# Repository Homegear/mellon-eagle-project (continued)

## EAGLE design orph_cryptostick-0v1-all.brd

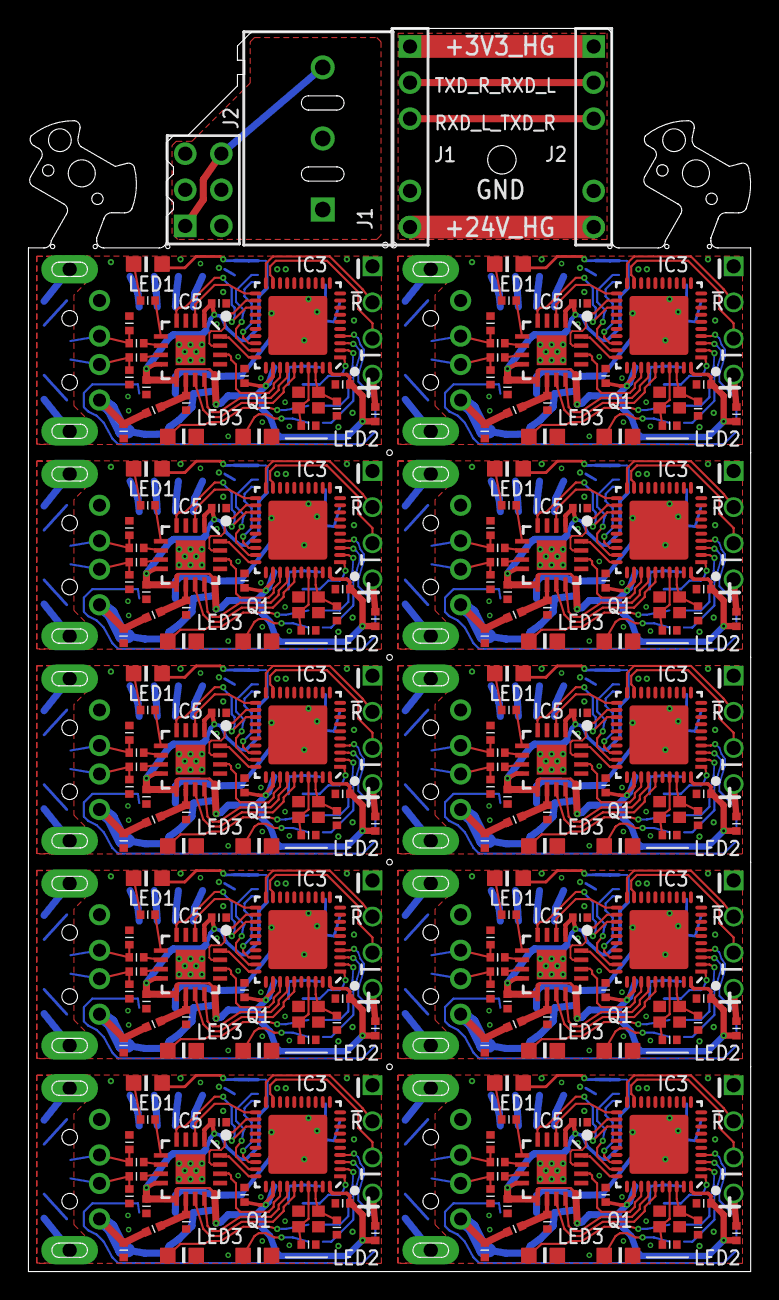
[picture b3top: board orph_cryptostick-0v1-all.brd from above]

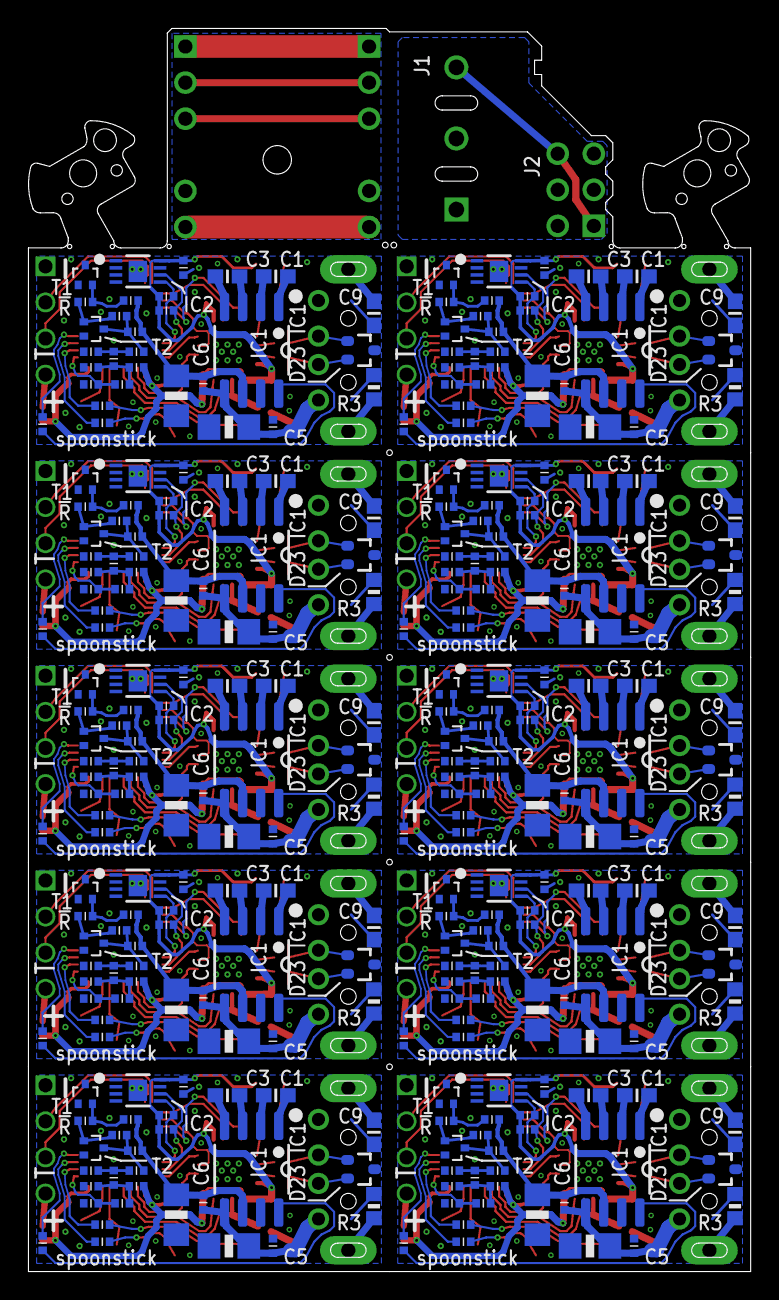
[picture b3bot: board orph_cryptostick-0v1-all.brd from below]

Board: 2 copper layers, 50.8 x 87.4 mm, 534 parts (300 on the bottom side), 428 nets.

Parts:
C1, C3, C23, C24, C47, C48, C68, C69, C89, C95, C115, C116, C136, C137, C157, C158, C178, C179, C199, C200: 0u22; C0603
C2, C4, C7, C10, C12, C16, C17, C18, C19, C20, C21, C25, C28, C30, C31, C33, C34, C40, C41, C42, C43, C44, C45, C49, C52, C54, C55, C61, C62, C63, C64, C65, C66, C70, C73, C75, C76, C82, C83, C84, C85, C86, C87, C92, C93, C94, C96, C99, C101, C102, C108, C109, C110, C111, C112, C113, C117, C120, C122, C123, C129, C130, C131, C132, C133, C134, C138, C141, C143, C144, C150, C151, C152, C153, C154, C155, C159, C162, C164, C165, C171, C172, C173, C174, C175, C176, C180, C183, C185, C186, C192, C193, C194, C195, C196, C197, C201, C204, C206, C207: 0u1; R0402-MCU
C5, C6, C26, C27, C50, C51, C71, C72, C97, C98, C118, C119, C139, C140, C160, C161, C181, C182, C202, C203: 10u/1206; C1206
C8, C11, C29, C35, C53, C56, C74, C77, C100, C103, C121, C124, C142, C145, C163, C166, C184, C187, C205, C208: 22p; R0402-MCU
C9, C36, C57, C78, C104, C125, C146, C167, C188, C209: 10n_nm; C0603
C13, C37, C58, C79, C105, C126, C147, C168, C189, C210: 10n; R0402-MCU
C14, C15, C38, C39, C59, C60, C80, C81, C90, C91, C106, C107, C127, C128, C148, C149, C169, C170, C190, C191: 47p; R0402-MCU
C22, C32, C46, C67, C88, C114, C135, C156, C177, C198: 100p; R0402-MCU
D1, D2, D3, D4, D5, D6, D7, D8, D9, D23: TVS-ESD7002; SC70-3
IC1, IC8, IC12, IC16, IC20, IC24, IC28, IC32, IC36, IC40: ST662-2; 8SOIC-2
IC2, IC6, IC10, IC14, IC18, IC22, IC26, IC30, IC34, IC38: ATECC508A-UDFN; 8UDFN
IC3, IC7, IC11, IC15, IC19, IC23, IC27, IC31, IC35, IC39: MSP430FR5959-40VQFN; 40VQFN-MSP430FR5959
IC4, IC5, IC9, IC13, IC17, IC21, IC25, IC29, IC33, IC37: FT230XQ; 16QFN-FT230X
J1, J7, J9, J11, J13, J15, J17, J19, J21, J23: USB-A-ST
J2: KLEMME-3POS-FEDER-5MM; KLEMME-FEDER-5MM-3POS
J3, J8, J10, J12, J14, J16, J18, J20, J22, J24: FE04-1
J4: FE03-2; FE03-2-R/A
J5, J6: MA06-1-KEY
L1, L2, L3, L4, L5, L6, L7, L8, L9, L10: R0402-MCU
LED1, LED2, LED4, LED5, LED7, LED8, LED10, LED11, LED13, LED14, LED16, LED17, LED19, LED20, LED22, LED23, LED25, LED26, LED28, LED29: green; 0603-SIDELED-RPI
LED3, LED6, LED9, LED12, LED15, LED18, LED21, LED24, LED27, LED30: orange; 0603-SIDELED-RPI
Q1, Q2, Q3, Q4, Q5, Q6, Q7, Q8, Q9, Q10: XTAL-30MHZ-2.0X1.6
R1, R4, R11, R12, R29, R30, R55, R56, R73, R77, R94, R95, R112, R113, R130, R131, R148, R149, R166, R167: 3k9; R0402-MCU
R2, R21, R47, R65, R86, R104, R122, R140, R158, R176: 4k7; R0402-MCU
R3, R22, R48, R66, R87, R105, R123, R141, R159, R177: 1M_nm; R0603
R5, R23, R49, R67, R88, R106, R124, R142, R160, R178: 68; R0402-MCU
R6, R7, R10, R24, R25, R28, R50, R51, R54, R68, R69, R72, R76, R89, R90, R93, R107, R108, R111, R125, R126, R129, R143, R144, R147, R161, R162, R165, R179, R180: 1k; R0402-MCU
R8, R9, R26, R27, R52, R53, R70, R71, R74, R75, R91, R92, R109, R110, R127, R128, R145, R146, R163, R164: 27; R0402-MCU
R13, R31, R33, R57, R78, R96, R114, R132, R150, R168: 100k; R0402-MCU
R14, R32, R34, R58, R79, R97, R115, R133, R151, R169: 1M; R0402-MCU
R15, R19, R35, R39, R41, R45, R59, R63, R80, R84, R98, R102, R116, R120, R134, R138, R152, R156, R170, R174: 10k; R0402-MCU
R16, R17, R18, R20, R36, R37, R38, R40, R42, R43, R44, R46, R60, R61, R62, R64, R81, R82, R83, R85, R99, R100, R101, R103, R117, R118, R119, R121, R135, R136, R137, R139, R153, R154, R155, R157, R171, R172, R173, R175: 33k; R0402-MCU
T1, T2, T3, T4, T5, T6, T7, T8, T9, T10, T11, T12, T13, T14, T15, T16, T17, T18, T19, T20: NPN-MMBT3904-SOT523; SOT523

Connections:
0V: J2.2, J4.3, J4.4
+3V3_FTDI: C2.1, C10.1, C12.1, C93.1, C94.1, IC2.8, IC3.32, IC3.40, IC5.1, IC5.8, IC5.9, LED1.A, R1.1, R4.1, R5.1, R36.1
+3V3_FTDI1: C17.1, C18.1, C19.1, C33.1, C34.1, IC4.1, IC4.8, IC4.9, IC6.8, IC7.32, IC7.40, LED4.A, R11.1, R12.1, R16.1, R23.1
+3V3_FTDI2: C41.1, C42.1, C43.1, C54.1, C55.1, IC9.1, IC9.8, IC9.9, IC10.8, IC11.32, IC11.40, LED7.A, R29.1, R30.1, R42.1, R49.1
+3V3_FTDI3: C62.1, C63.1, C64.1, C75.1, C76.1, IC13.1, IC13.8, IC13.9, IC14.8, IC15.32, IC15.40, LED10.A, R55.1, R56.1, R60.1, R67.1
+3V3_FTDI4: C83.1, C84.1, C85.1, C101.1, C102.1, IC17.1, IC17.8, IC17.9, IC18.8, IC19.32, IC19.40, LED13.A, R73.1, R77.1, R81.1, R88.1
+3V3_FTDI5: C109.1, C110.1, C111.1, C122.1, C123.1, IC21.1, IC21.8, IC21.9, IC22.8, IC23.32, IC23.40, LED16.A, R94.1, R95.1, R99.1, R106.1
+3V3_FTDI6: C130.1, C131.1, C132.1, C143.1, C144.1, IC25.1, IC25.8, IC25.9, IC26.8, IC27.32, IC27.40, LED19.A, R112.1, R113.1, R117.1, R124.1
+3V3_FTDI7: C151.1, C152.1, C153.1, C164.1, C165.1, IC29.1, IC29.8, IC29.9, IC30.8, IC31.32, IC31.40, LED22.A, R130.1, R131.1, R135.1, R142.1
+3V3_FTDI8: C172.1, C173.1, C174.1, C185.1, C186.1, IC33.1, IC33.8, IC33.9, IC34.8, IC35.32, IC35.40, LED25.A, R148.1, R149.1, R153.1, R160.1
+3V3_FTDI9: C193.1, C194.1, C195.1, C206.1, C207.1, IC37.1, IC37.8, IC37.9, IC38.8, IC39.32, IC39.40, LED28.A, R166.1, R167.1, R171.1, R178.1
+3V3_HG: J5.1, J6.1
+5V_FTDI: C92.1, IC5.10, L1.2
+5V_FTDI1: C16.1, IC4.10, L2.2
+5V_FTDI2: C40.1, IC9.10, L3.2
+5V_FTDI3: C61.1, IC13.10, L4.2
+5V_FTDI4: C82.1, IC17.10, L5.2
+5V_FTDI5: C108.1, IC21.10, L6.2
+5V_FTDI6: C129.1, IC25.10, L7.2
+5V_FTDI7: C150.1, IC29.10, L8.2
+5V_FTDI8: C171.1, IC33.10, L9.2
+5V_FTDI9: C192.1, IC37.10, L10.2
+12V: C4.1, C6.1, IC1.6, R33.2, R35.1
+12V1: C25.1, C27.1, IC8.6, R13.2, R15.1
+12V2: C49.1, C51.1, IC12.6, R31.2, R41.1
+12V3: C70.1, C72.1, IC16.6, R57.2, R59.1
+12V4: C96.1, C98.1, IC20.6, R78.2, R80.1
+12V5: C117.1, C119.1, IC24.6, R96.2, R98.1
+12V6: C138.1, C140.1, IC28.6, R114.2, R116.1
+12V7: C159.1, C161.1, IC32.6, R132.2, R134.1
+12V8: C180.1, C182.1, IC36.6, R150.2, R152.1
+12V9: C201.1, C203.1, IC40.6, R168.2, R170.1
+24V: J2.1, J4.2, J4.5
+24V_HG: J5.6, J6.6
+VBUS: C4.2, C5.1, C7.1, C13.1, IC1.5, J1.1, L1.1
+VBUS1: C25.2, C26.1, C28.1, C37.1, IC8.5, J7.1, L2.1
+VBUS2: C49.2, C50.1, C52.1, C58.1, IC12.5, J9.1, L3.1
+VBUS3: C70.2, C71.1, C73.1, C79.1, IC16.5, J11.1, L4.1
+VBUS4: C96.2, C97.1, C99.1, C105.1, IC20.5, J13.1, L5.1
+VBUS5: C117.2, C118.1, C120.1, C126.1, IC24.5, J15.1, L6.1
+VBUS6: C138.2, C139.1, C141.1, C147.1, IC28.5, J17.1, L7.1
+VBUS7: C159.2, C160.1, C162.1, C168.1, IC32.5, J19.1, L8.1
+VBUS8: C180.2, C181.1, C183.1, C189.1, IC36.5, J21.1, L9.1
+VBUS9: C201.2, C202.1, C204.1, C210.1, IC40.5, J23.1, L10.1
CHARGEPUMP_SHDN: IC3.4, R2.2
CHARGEPUMP_SHDN1: IC7.4, R21.2
CHARGEPUMP_SHDN2: IC11.4, R47.2
CHARGEPUMP_SHDN3: IC15.4, R65.2
CHARGEPUMP_SHDN4: IC19.4, R86.2
CHARGEPUMP_SHDN5: IC23.4, R104.2
CHARGEPUMP_SHDN6: IC27.4, R122.2
CHARGEPUMP_SHDN7: IC31.4, R140.2
CHARGEPUMP_SHDN8: IC35.4, R158.2
CHARGEPUMP_SHDN9: IC39.4, R176.2
FTDI_CBUS0: IC3.34, IC5.12
FTDI_CBUS1: IC3.35, IC5.11
FTDI_CBUS2: IC4.11, IC7.35
FTDI_CBUS3: IC4.12, IC7.34
FTDI_CBUS4: IC9.11, IC11.35
FTDI_CBUS5: IC9.12, IC11.34
FTDI_CBUS6: IC13.11, IC15.35
FTDI_CBUS7: IC13.12, IC15.34
FTDI_CBUS8: IC17.11, IC19.35
FTDI_CBUS9: IC17.12, IC19.34
FTDI_CBUS10: IC21.11, IC23.35
FTDI_CBUS11: IC21.12, IC23.34
FTDI_CBUS12: IC25.11, IC27.35
FTDI_CBUS13: IC25.12, IC27.34
FTDI_CBUS14: IC29.11, IC31.35
FTDI_CBUS15: IC29.12, IC31.34
FTDI_CBUS16: IC33.11, IC35.35
FTDI_CBUS17: IC33.12, IC35.34
FTDI_CBUS18: IC37.11, IC39.35
FTDI_CBUS19: IC37.12, IC39.34
FTDI_CTS#: IC3.23, IC5.4
FTDI_CTS#1: IC4.4, IC7.23
FTDI_CTS#2: IC9.4, IC11.23
FTDI_CTS#3: IC13.4, IC15.23
FTDI_CTS#4: IC17.4, IC19.23
FTDI_CTS#5: IC21.4, IC23.23
FTDI_CTS#6: IC25.4, IC27.23
FTDI_CTS#7: IC29.4, IC31.23
FTDI_CTS#8: IC33.4, IC35.23
FTDI_CTS#9: IC37.4, IC39.23
FTDI_RTS#: IC3.30, IC5.16
FTDI_RTS#1: IC4.16, IC7.30
FTDI_RTS#2: IC9.16, IC11.30
FTDI_RTS#3: IC13.16, IC15.30
FTDI_RTS#4: IC17.16, IC19.30
FTDI_RTS#5: IC21.16, IC23.30
FTDI_RTS#6: IC25.16, IC27.30
FTDI_RTS#7: IC29.16, IC31.30
FTDI_RTS#8: IC33.16, IC35.30
FTDI_RTS#9: IC37.16, IC39.30
FTDI_RXD: IC3.21, IC5.2
FTDI_RXD1: IC4.2, IC7.21
FTDI_RXD2: IC9.2, IC11.21
FTDI_RXD3: IC13.2, IC15.21
FTDI_RXD4: IC17.2, IC19.21
FTDI_RXD5: IC21.2, IC23.21
FTDI_RXD6: IC25.2, IC27.21
FTDI_RXD7: IC29.2, IC31.21
FTDI_RXD8: IC33.2, IC35.21
FTDI_RXD9: IC37.2, IC39.21
FTDI_TXD: IC3.22, IC5.15
FTDI_TXD1: IC4.15, IC7.22
FTDI_TXD2: IC9.15, IC11.22
FTDI_TXD3: IC13.15, IC15.22
FTDI_TXD4: IC17.15, IC19.22
FTDI_TXD5: IC21.15, IC23.22
FTDI_TXD6: IC25.15, IC27.22
FTDI_TXD7: IC29.15, IC31.22
FTDI_TXD8: IC33.15, IC35.22
FTDI_TXD9: IC37.15, IC39.22
FTDI_TXLED#: IC5.5, R76.1
FTDI_TXLED#1: IC4.5, R10.1
FTDI_TXLED#2: IC9.5, R28.1
FTDI_TXLED#3: IC13.5, R54.1
FTDI_TXLED#4: IC17.5, R72.1
FTDI_TXLED#5: IC21.5, R93.1
FTDI_TXLED#6: IC25.5, R111.1
FTDI_TXLED#7: IC29.5, R129.1
FTDI_TXLED#8: IC33.5, R147.1
FTDI_TXLED#9: IC37.5, R165.1
GND: C2.2, C5.2, C6.2, C7.2, C8.1, C9.1, C10.2, C11.1, C12.2, C13.2, C32.2, C90.2, C91.2, C92.2, C93.2, C94.2, D23.3, IC1.7, IC2.1, IC2.2, IC2.3, IC2.4, IC2.7, IC2.EP, IC3.31, IC3.36, IC3.39, IC3.EP, IC5.3, IC5.13, IC5.EP, J1.4, J3.1, LED2.C, LED3.C, Q1.2, Q1.4, R3.1, R37.2, R39.2, T1.1, T2.2
GND1: J5.5, J6.5
GND2: C14.2, C15.2, C16.2, C17.2, C18.2, C19.2, C22.2, C26.2, C27.2, C28.2, C29.1, C33.2, C34.2, C35.1, C36.1, C37.2, D1.3, IC4.3, IC4.13, IC4.EP, IC6.1, IC6.2, IC6.3, IC6.4, IC6.7, IC6.EP, IC7.31, IC7.36, IC7.39, IC7.EP, IC8.7, J7.4, J8.1, LED5.C, LED6.C, Q2.2, Q2.4, R17.2, R19.2, R22.1, T3.1, T4.2
GND3: C38.2, C39.2, C40.2, C41.2, C42.2, C43.2, C46.2, C50.2, C51.2, C52.2, C53.1, C54.2, C55.2, C56.1, C57.1, C58.2, D2.3, IC9.3, IC9.13, IC9.EP, IC10.1, IC10.2, IC10.3, IC10.4, IC10.7, IC10.EP, IC11.31, IC11.36, IC11.39, IC11.EP, IC12.7, J9.4, J10.1, LED8.C, LED9.C, Q3.2, Q3.4, R43.2, R45.2, R48.1, T5.1, T6.2
GND4: C59.2, C60.2, C61.2, C62.2, C63.2, C64.2, C67.2, C71.2, C72.2, C73.2, C74.1, C75.2, C76.2, C77.1, C78.1, C79.2, D3.3, IC13.3, IC13.13, IC13.EP, IC14.1, IC14.2, IC14.3, IC14.4, IC14.7, IC14.EP, IC15.31, IC15.36, IC15.39, IC15.EP, IC16.7, J11.4, J12.1, LED11.C, LED12.C, Q4.2, Q4.4, R61.2, R63.2, R66.1, T7.1, T8.2
GND5: C80.2, C81.2, C82.2, C83.2, C84.2, C85.2, C88.2, C97.2, C98.2, C99.2, C100.1, C101.2, C102.2, C103.1, C104.1, C105.2, D4.3, IC17.3, IC17.13, IC17.EP, IC18.1, IC18.2, IC18.3, IC18.4, IC18.7, IC18.EP, IC19.31, IC19.36, IC19.39, IC19.EP, IC20.7, J13.4, J14.1, LED14.C, LED15.C, Q5.2, Q5.4, R82.2, R84.2, R87.1, T9.1, T10.2
GND6: C106.2, C107.2, C108.2, C109.2, C110.2, C111.2, C114.2, C118.2, C119.2, C120.2, C121.1, C122.2, C123.2, C124.1, C125.1, C126.2, D5.3, IC21.3, IC21.13, IC21.EP, IC22.1, IC22.2, IC22.3, IC22.4, IC22.7, IC22.EP, IC23.31, IC23.36, IC23.39, IC23.EP, IC24.7, J15.4, J16.1, LED17.C, LED18.C, Q6.2, Q6.4, R100.2, R102.2, R105.1, T11.1, T12.2
GND7: C127.2, C128.2, C129.2, C130.2, C131.2, C132.2, C135.2, C139.2, C140.2, C141.2, C142.1, C143.2, C144.2, C145.1, C146.1, C147.2, D6.3, IC25.3, IC25.13, IC25.EP, IC26.1, IC26.2, IC26.3, IC26.4, IC26.7, IC26.EP, IC27.31, IC27.36, IC27.39, IC27.EP, IC28.7, J17.4, J18.1, LED20.C, LED21.C, Q7.2, Q7.4, R118.2, R120.2, R123.1, T13.1, T14.2
GND8: C148.2, C149.2, C150.2, C151.2, C152.2, C153.2, C156.2, C160.2, C161.2, C162.2, C163.1, C164.2, C165.2, C166.1, C167.1, C168.2, D7.3, IC29.3, IC29.13, IC29.EP, IC30.1, IC30.2, IC30.3, IC30.4, IC30.7, IC30.EP, IC31.31, IC31.36, IC31.39, IC31.EP, IC32.7, J19.4, J20.1, LED23.C, LED24.C, Q8.2, Q8.4, R136.2, R138.2, R141.1, T15.1, T16.2
GND9: C169.2, C170.2, C171.2, C172.2, C173.2, C174.2, C177.2, C181.2, C182.2, C183.2, C184.1, C185.2, C186.2, C187.1, C188.1, C189.2, D8.3, IC33.3, IC33.13, IC33.EP, IC34.1, IC34.2, IC34.3, IC34.4, IC34.7, IC34.EP, IC35.31, IC35.36, IC35.39, IC35.EP, IC36.7, J21.4, J22.1, LED26.C, LED27.C, Q9.2, Q9.4, R154.2, R156.2, R159.1, T17.1, T18.2
GND10: C190.2, C191.2, C192.2, C193.2, C194.2, C195.2, C198.2, C202.2, C203.2, C204.2, C205.1, C206.2, C207.2, C208.1, C209.1, C210.2, D9.3, IC37.3, IC37.13, IC37.EP, IC38.1, IC38.2, IC38.3, IC38.4, IC38.7, IC38.EP, IC39.31, IC39.36, IC39.39, IC39.EP, IC40.7, J23.4, J24.1, LED29.C, LED30.C, Q10.2, Q10.4, R172.2, R174.2, R177.1, T19.1, T20.2
LED_GREEN: IC3.3, R6.2
LED_GREEN1: IC7.3, R24.2
LED_GREEN2: IC11.3, R50.2
LED_GREEN3: IC15.3, R68.2
LED_GREEN4: IC19.3, R89.2
LED_GREEN5: IC23.3, R107.2
LED_GREEN6: IC27.3, R125.2
LED_GREEN7: IC31.3, R143.2
LED_GREEN8: IC35.3, R161.2
LED_GREEN9: IC39.3, R179.2
LED_ORANGE: IC3.2, R7.2
LED_ORANGE1: IC7.2, R25.2
LED_ORANGE2: IC11.2, R51.2
LED_ORANGE3: IC15.2, R69.2
LED_ORANGE4: IC19.2, R90.2
LED_ORANGE5: IC23.2, R108.2
LED_ORANGE6: IC27.2, R126.2
LED_ORANGE7: IC31.2, R144.2
LED_ORANGE8: IC35.2, R162.2
LED_ORANGE9: IC39.2, R180.2
unnamed: J3.4, R5.2
unnamed: C31.1, R34.2, T2.1
unnamed: LED3.A, R7.1
unnamed: LED2.A, R6.1
unnamed: R34.1, R35.2, R38.1, T2.3
unnamed: C3.1, IC1.3
unnamed: C1.2, IC1.2
unnamed: C1.1, IC1.1
unnamed: C3.2, IC1.4
unnamed: LED1.C, R76.2
unnamed: C11.2, IC3.38, Q1.1
unnamed: IC1.8, R2.1
unnamed: C8.2, IC3.37, Q1.3
unnamed: IC4.7, R8.1
unnamed: IC4.6, R9.1
unnamed: C14.1, D1.1, J7.3, R9.2
unnamed: C15.1, D1.2, J7.2, R8.2
unnamed: LED4.C, R10.2
unnamed: C20.2, R13.1, T3.2
unnamed: C20.1, R14.2, T4.1
unnamed: R14.1, R15.2, R18.1, T4.3
unnamed: C21.1, R16.2, R17.1, R20.1
unnamed: C21.2, R18.2, R19.1
unnamed: C24.1, IC8.3
unnamed: C23.2, IC8.2
unnamed: C23.1, IC8.1
unnamed: C24.2, IC8.4
unnamed: IC8.8, R21.1
unnamed: C35.2, IC7.38, Q2.1
unnamed: C29.2, IC7.37, Q2.3
unnamed: J8.4, R23.2
unnamed: LED6.A, R25.1
unnamed: LED5.A, R24.1
unnamed: IC9.7, R26.1
unnamed: C31.2, R33.1, T1.2
unnamed: IC9.6, R27.1
unnamed: C38.1, D2.1, J9.3, R27.2
unnamed: C39.1, D2.2, J9.2, R26.2
unnamed: IC5.7, R75.1
unnamed: IC5.6, R74.1
unnamed: LED7.C, R28.2
unnamed: C30.1, R36.2, R37.1, R40.1
unnamed: C30.2, R38.2, R39.1
unnamed: C44.2, R31.1, T5.2
unnamed: C44.1, R32.2, T6.1
unnamed: R32.1, R41.2, R44.1, T6.3
unnamed: C45.1, R42.2, R43.1, R46.1
unnamed: C45.2, R44.2, R45.1
unnamed: C48.1, IC12.3
unnamed: C47.2, IC12.2
unnamed: C47.1, IC12.1
unnamed: C48.2, IC12.4
unnamed: IC12.8, R47.1
unnamed: C56.2, IC11.38, Q3.1
unnamed: C53.2, IC11.37, Q3.3
unnamed: J10.4, R49.2
unnamed: LED9.A, R51.1
unnamed: LED8.A, R50.1
unnamed: IC13.7, R52.1
unnamed: IC13.6, R53.1
unnamed: C59.1, D3.1, J11.3, R53.2
unnamed: C60.1, D3.2, J11.2, R52.2
unnamed: LED10.C, R54.2
unnamed: C65.2, R57.1, T7.2
unnamed: C65.1, R58.2, T8.1
unnamed: R58.1, R59.2, R62.1, T8.3
unnamed: C66.1, R60.2, R61.1, R64.1
unnamed: C66.2, R62.2, R63.1
unnamed: C69.1, IC16.3
unnamed: C68.2, IC16.2
unnamed: C68.1, IC16.1
unnamed: C69.2, IC16.4
unnamed: IC16.8, R65.1
unnamed: C77.2, IC15.38, Q4.1
unnamed: C91.1, D23.1, J1.3, R74.2
unnamed: C90.1, D23.2, J1.2, R75.2
unnamed: C74.2, IC15.37, Q4.3
unnamed: J12.4, R67.2
unnamed: LED12.A, R69.1
unnamed: LED11.A, R68.1
unnamed: IC17.7, R70.1
unnamed: IC17.6, R71.1
unnamed: C80.1, D4.1, J13.3, R71.2
unnamed: C81.1, D4.2, J13.2, R70.2
unnamed: LED13.C, R72.2
unnamed: C86.2, R78.1, T9.2
unnamed: C86.1, R79.2, T10.1
unnamed: R79.1, R80.2, R83.1, T10.3
unnamed: C87.1, R81.2, R82.1, R85.1
unnamed: C87.2, R83.2, R84.1
unnamed: C95.1, IC20.3
unnamed: C89.2, IC20.2
unnamed: C89.1, IC20.1
unnamed: C95.2, IC20.4
unnamed: IC20.8, R86.1
unnamed: C103.2, IC19.38, Q5.1
unnamed: C100.2, IC19.37, Q5.3
unnamed: J14.4, R88.2
unnamed: LED15.A, R90.1
unnamed: LED14.A, R89.1
unnamed: IC21.7, R91.1
unnamed: IC21.6, R92.1
unnamed: C106.1, D5.1, J15.3, R92.2
unnamed: C107.1, D5.2, J15.2, R91.2
unnamed: LED16.C, R93.2
unnamed: C112.2, R96.1, T11.2
unnamed: C112.1, R97.2, T12.1
unnamed: R97.1, R98.2, R101.1, T12.3
unnamed: C113.1, R99.2, R100.1, R103.1
unnamed: C113.2, R101.2, R102.1
unnamed: C116.1, IC24.3
unnamed: C115.2, IC24.2
unnamed: C115.1, IC24.1
unnamed: C116.2, IC24.4
unnamed: IC24.8, R104.1
unnamed: C124.2, IC23.38, Q6.1
unnamed: C121.2, IC23.37, Q6.3
unnamed: J16.4, R106.2
unnamed: LED18.A, R108.1
unnamed: LED17.A, R107.1
unnamed: IC25.7, R109.1
unnamed: IC25.6, R110.1
unnamed: C127.1, D6.1, J17.3, R110.2
unnamed: C128.1, D6.2, J17.2, R109.2
unnamed: LED19.C, R111.2
unnamed: C133.2, R114.1, T13.2
unnamed: C133.1, R115.2, T14.1
unnamed: R115.1, R116.2, R119.1, T14.3
unnamed: C134.1, R117.2, R118.1, R121.1
unnamed: C134.2, R119.2, R120.1
unnamed: C137.1, IC28.3
unnamed: C136.2, IC28.2
unnamed: C136.1, IC28.1
unnamed: C137.2, IC28.4
unnamed: IC28.8, R122.1
unnamed: C145.2, IC27.38, Q7.1
unnamed: C142.2, IC27.37, Q7.3
unnamed: J18.4, R124.2
unnamed: LED21.A, R126.1
unnamed: LED20.A, R125.1
unnamed: IC29.7, R127.1
unnamed: IC29.6, R128.1
unnamed: C148.1, D7.1, J19.3, R128.2
unnamed: C149.1, D7.2, J19.2, R127.2
unnamed: LED22.C, R129.2
unnamed: C154.2, R132.1, T15.2
unnamed: C154.1, R133.2, T16.1
unnamed: R133.1, R134.2, R137.1, T16.3
unnamed: C155.1, R135.2, R136.1, R139.1
unnamed: C155.2, R137.2, R138.1
unnamed: C158.1, IC32.3
unnamed: C157.2, IC32.2
unnamed: C157.1, IC32.1
unnamed: C158.2, IC32.4
unnamed: IC32.8, R140.1
unnamed: C166.2, IC31.38, Q8.1
unnamed: C163.2, IC31.37, Q8.3
unnamed: J20.4, R142.2
unnamed: LED24.A, R144.1
unnamed: LED23.A, R143.1
unnamed: IC33.7, R145.1
unnamed: IC33.6, R146.1
unnamed: C169.1, D8.1, J21.3, R146.2
unnamed: C170.1, D8.2, J21.2, R145.2
unnamed: LED25.C, R147.2
unnamed: C175.2, R150.1, T17.2
unnamed: C175.1, R151.2, T18.1
unnamed: R151.1, R152.2, R155.1, T18.3
unnamed: C176.1, R153.2, R154.1, R157.1
unnamed: C176.2, R155.2, R156.1
unnamed: C179.1, IC36.3
unnamed: C178.2, IC36.2
unnamed: C178.1, IC36.1
unnamed: C179.2, IC36.4
unnamed: IC36.8, R158.1
unnamed: C187.2, IC35.38, Q9.1
unnamed: C184.2, IC35.37, Q9.3
unnamed: J22.4, R160.2
unnamed: LED27.A, R162.1
unnamed: LED26.A, R161.1
unnamed: IC37.7, R163.1
unnamed: IC37.6, R164.1
unnamed: C190.1, D9.1, J23.3, R164.2
unnamed: C191.1, D9.2, J23.2, R163.2
unnamed: LED28.C, R165.2
unnamed: C196.2, R168.1, T19.2
unnamed: C196.1, R169.2, T20.1
unnamed: R169.1, R170.2, R173.1, T20.3
unnamed: C197.1, R171.2, R172.1, R175.1
unnamed: C197.2, R173.2, R174.1
unnamed: C200.1, IC40.3
unnamed: C199.2, IC40.2
unnamed: C199.1, IC40.1
unnamed: C200.2, IC40.4
unnamed: IC40.8, R176.1
unnamed: C208.2, IC39.38, Q10.1
unnamed: C205.2, IC39.37, Q10.3
unnamed: J24.4, R178.2
unnamed: LED30.A, R180.1
unnamed: LED29.A, R179.1
NOISE: C32.1, IC3.1, R40.2
NOISE1: C22.1, IC7.1, R20.2
NOISE2: C46.1, IC11.1, R46.2
NOISE3: C67.1, IC15.1, R64.2
NOISE4: C88.1, IC19.1, R85.2
NOISE5: C114.1, IC23.1, R103.2
NOISE6: C135.1, IC27.1, R121.2
NOISE7: C156.1, IC31.1, R139.2
NOISE8: C177.1, IC35.1, R157.2
NOISE9: C198.1, IC39.1, R175.2
PE: J2.3, J4.1, J4.6
RESET#: IC3.20, J3.2
RESET#1: IC7.20, J8.2
RESET#2: IC11.20, J10.2
RESET#3: IC15.20, J12.2
RESET#4: IC19.20, J14.2
RESET#5: IC23.20, J16.2
RESET#6: IC27.20, J18.2
RESET#7: IC31.20, J20.2
RESET#8: IC35.20, J22.2
RESET#9: IC39.20, J24.2
RXD_L_TXD_R: J5.3, J6.3
SCL: IC2.6, IC3.29, R4.2
SCL1: IC6.6, IC7.29, R12.2
SCL2: IC10.6, IC11.29, R30.2
SCL3: IC14.6, IC15.29, R56.2
SCL4: IC18.6, IC19.29, R77.2
SCL5: IC22.6, IC23.29, R95.2
SCL6: IC26.6, IC27.29, R113.2
SCL7: IC30.6, IC31.29, R131.2
SCL8: IC34.6, IC35.29, R149.2
SCL9: IC38.6, IC39.29, R167.2
SDA: IC2.5, IC3.28, R1.2
SDA1: IC6.5, IC7.28, R11.2
SDA2: IC10.5, IC11.28, R29.2
SDA3: IC14.5, IC15.28, R55.2
SDA4: IC18.5, IC19.28, R73.2
SDA5: IC22.5, IC23.28, R94.2
SDA6: IC26.5, IC27.28, R112.2
SDA7: IC30.5, IC31.28, R130.2
SDA8: IC34.5, IC35.28, R148.2
SDA9: IC38.5, IC39.28, R166.2
TEST: IC3.19, J3.3
TEST1: IC7.19, J8.3
TEST2: IC11.19, J10.3
TEST3: IC15.19, J12.3
TEST4: IC19.19, J14.3
TEST5: IC23.19, J16.3
TEST6: IC27.19, J18.3
TEST7: IC31.19, J20.3
TEST8: IC35.19, J22.3
TEST9: IC39.19, J24.3
TXD_R_RXD_L: J5.2, J6.2
USB_SHLD: C9.2, J1.SH1, J1.SH2, R3.2
USB_SHLD1: C36.2, J7.SH1, J7.SH2, R22.2
USB_SHLD2: C57.2, J9.SH1, J9.SH2, R48.2
USB_SHLD3: C78.2, J11.SH1, J11.SH2, R66.2
USB_SHLD4: C104.2, J13.SH1, J13.SH2, R87.2
USB_SHLD5: C125.2, J15.SH1, J15.SH2, R105.2
USB_SHLD6: C146.2, J17.SH1, J17.SH2, R123.2
USB_SHLD7: C167.2, J19.SH1, J19.SH2, R141.2
USB_SHLD8: C188.2, J21.SH1, J21.SH2, R159.2
USB_SHLD9: C209.2, J23.SH1, J23.SH2, R177.2
USB_SLEEP#: IC3.33, IC5.14
USB_SLEEP#1: IC4.14, IC7.33
USB_SLEEP#2: IC9.14, IC11.33
USB_SLEEP#3: IC13.14, IC15.33
USB_SLEEP#4: IC17.14, IC19.33
USB_SLEEP#5: IC21.14, IC23.33
USB_SLEEP#6: IC25.14, IC27.33
USB_SLEEP#7: IC29.14, IC31.33
USB_SLEEP#8: IC33.14, IC35.33
USB_SLEEP#9: IC37.14, IC39.33
